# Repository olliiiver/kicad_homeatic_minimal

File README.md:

## Homematic minimal PCB

A minimal PCB to build hardware devices for Homematic / BidCoS networks.

PINs (A0x - D0x, GND, 3v3) are compatible to 2.54mm prototype perfboards.

Upload is possible via Serial (FTDI,etc) and ISP (J3).

## BOM

- Case: RND 455-00192
  https://www.reichelt.de/polycarbonate-box-w-clear-lid-rnd-455-00192-p193406.html

- ATmega328P-AU
  http://ww1.microchip.com/downloads/en/DeviceDoc/Atmel-7810-Automotive-Microcontrollers-ATmega328P_Datasheet.pdf
  https://www.reichelt.de/atmega-avr-risc-controller-tqfp-32-atmega-328p-au-p119684.html
  
- Switch: RND 210-00204
  https://www.reichelt.de/pcb-tactile-switches-rnd-210-00204-p226425.html
  
- C 0805: 22 pF, 100pF
  https://www.reichelt.de/mlcc-0805-22-pf-200-v-5-rnd-1500805n2203-p226114.html
    
- LED 0805
  https://www.reichelt.de/led-smd-0805-green-7-1-mcd-160-oso-lgr971-p231718.html

  - R 0805: 330 Ohm, 1k Ohm, etc

  - CC1101 module from ebay

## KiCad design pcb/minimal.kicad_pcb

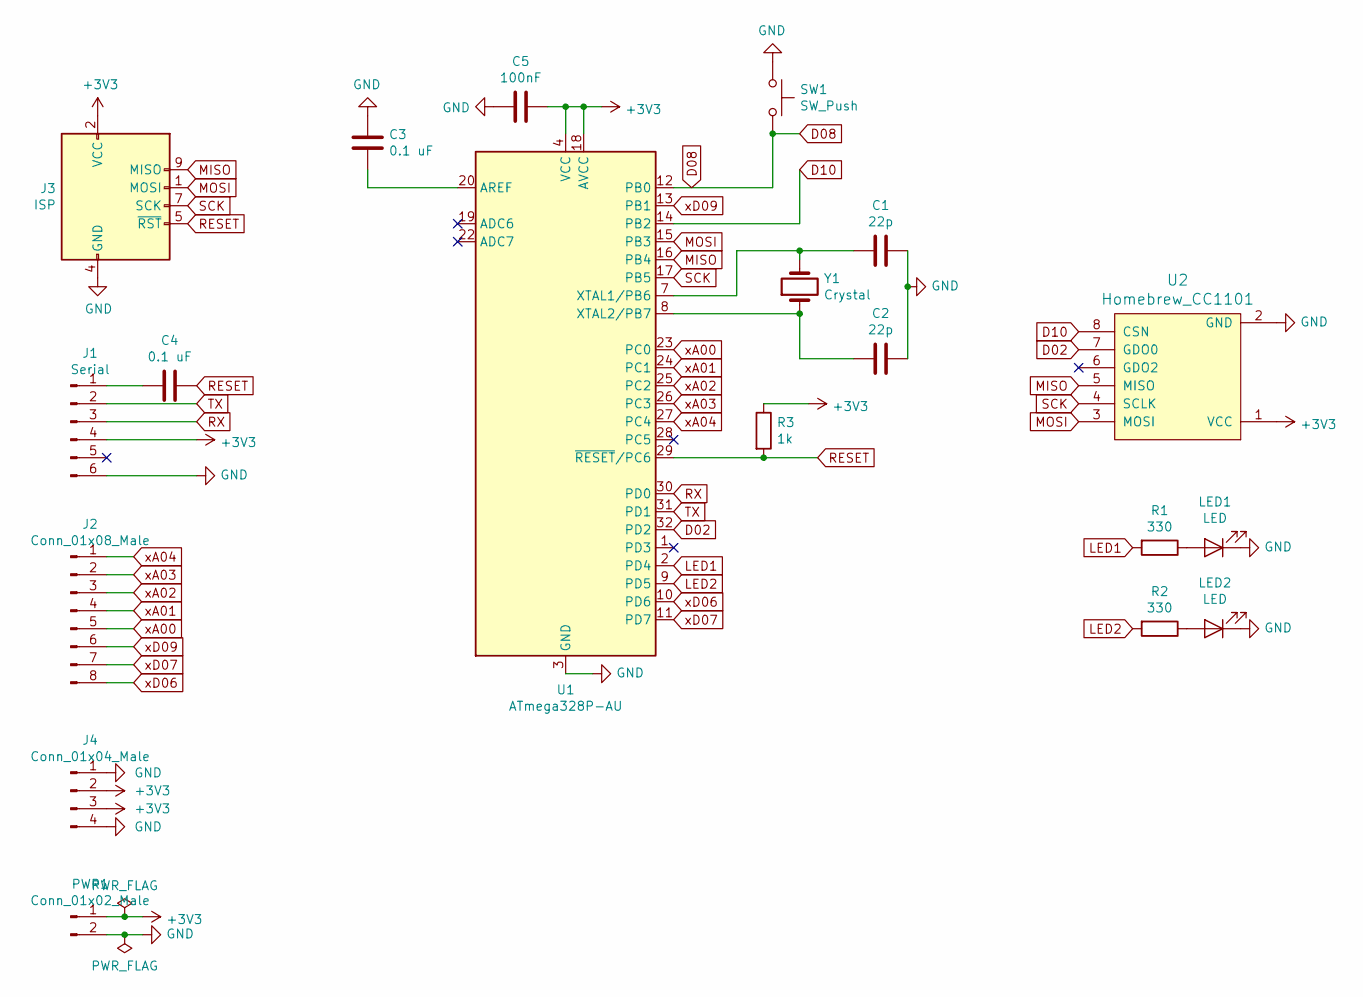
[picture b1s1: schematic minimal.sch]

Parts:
C1, C2: 22p; C_0805_2012Metric_Pad1.15x1.40mm_HandSolder
C3, C4: 0.1 uF; C_0805_2012Metric_Pad1.15x1.40mm_HandSolder
C5: 100nF; C_0805_2012Metric_Pad1.15x1.40mm_HandSolder
J1: Serial; PinHeader_1x06_P2.54mm_Vertical
J2: Conn_01x08_Male; PinHeader_1x08_P2.54mm_Vertical
J3: ISP; PinHeader_2x05_P2.54mm_Vertical
J4: Conn_01x04_Male; PinHeader_1x04_P2.54mm_Vertical
LED1, LED2: LED; LED_0805_2012Metric_Pad1.15x1.40mm_HandSolder
PWR1: Conn_01x02_Male; PinHeader_1x02_P2.54mm_Vertical
R1, R2: 330; R_0805_2012Metric_Pad1.15x1.40mm_HandSolder
R3: 1k; R_0805_2012Metric_Pad1.15x1.40mm_HandSolder
SW1: SW_Push; SW_Push_1P1T_NO_6x6mm_H9.5mm
U1: ATmega328P-AU; TQFP-32_7x7mm_P0.8mm
U2: Homebrew_CC1101; cc1101
Y1: Crystal; Crystal_HC49-4H_Vertical

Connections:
+3V3: C5.1, J1.4, J3.2 (VCC), J4.2, J4.3, PWR1.1, R3.1, U1.4 (VCC), U1.6 (VCC), U1.18 (AVCC), U2.1 (VCC)
D02: U1.32 (PD2), U2.7 (GDO0)
D08: SW1.2, U1.12 (PB0)
D10: U1.14 (PB2), U2.8 (CSN)
GND: C1.1, C2.1, C3.1, C5.2, J1.6, J3.4 (GND), J3.6 (GND), J3.8 (GND), J3.10 (GND), J4.1, J4.4, LED1.1 (K), LED2.1 (K), PWR1.2, SW1.1, U1.3 (GND), U1.5 (GND), U1.21 (GND), U2.2 (GND)
LED1: R1.2, U1.2 (PD4)
LED2: R2.2, U1.9 (PD5)
MISO: J3.9 (MISO), U1.16 (PB4), U2.5 (MISO)
MOSI: J3.1 (MOSI), U1.15 (PB3), U2.3 (MOSI)
unnamed: C1.2, U1.7 (XTAL1/PB6), Y1.2
unnamed: C2.2, U1.8 (XTAL2/PB7), Y1.1
unnamed: C3.2, U1.20 (AREF)
unnamed: C4.2, J1.1
unnamed: LED1.2 (A), R1.1
unnamed: LED2.2 (A), R2.1
RESET: C4.1, J3.5 (~RST), R3.2, U1.29 (~RESET~/PC6)
RX: J1.3, U1.30 (PD0)
SCK: J3.7 (SCK), U1.17 (PB5), U2.4 (SCLK)
TX: J1.2, U1.31 (PD1)
xA00: J2.5, U1.23 (PC0)
xA01: J2.4, U1.24 (PC1)
xA02: J2.3, U1.25 (PC2)
xA03: J2.2, U1.26 (PC3)
xA04: J2.1, U1.27 (PC4)
xD06: J2.8, U1.10 (PD6)
xD07: J2.7, U1.11 (PD7)
xD09: J2.6, U1.13 (PB1)

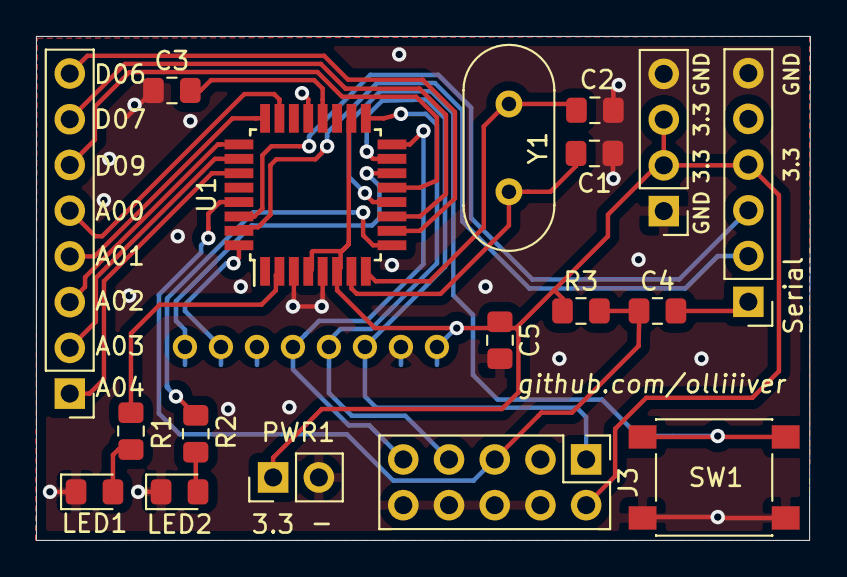
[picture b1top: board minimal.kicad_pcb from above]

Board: 2 copper layers, 43.0 x 28.0 mm, 19 parts (1 on the bottom side), 27 nets.

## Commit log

2020-10-26 Initial
